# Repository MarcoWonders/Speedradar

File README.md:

# MAR07 SpeedRadar

A battery-powered Doppler speed radar that stands next to (or behind) a long jump runway and shows the athlete's approach speed on a TFT display. The goal is to see whether the run-up speed is consistent from jump to jump.

> **Status: work in progress.** The schematic is complete. The PCB (4 layers, 111 × 49 mm, 4 × M3 holes on a 103 × 41 mm pattern) is routed and passes DRC with no unconnected items. The first boards (V1) were ordered at JLCPCB on 17 November 2026; the fabrication files are in `20_Hardware/MAR07_SpeedRadar/production/`. A first enclosure design exists (see below). A first firmware compiles but has not run on hardware. Nothing has been assembled or tested yet.

## How it works

A CDM324 24 GHz Doppler module outputs a low-level IF signal whose frequency is proportional to the target's radial speed:

```
f_d = 2 · v · f0 / c  ≈  161 Hz per m/s   (f0 = 24.125 GHz)
```

A long jump approach peaks at about 8 to 11 m/s, so the signal of interest is roughly 100 Hz to 1.8 kHz. The analog front end amplifies it, a microcontroller samples it, and an FFT picks out the peak frequency.

| Block | Part | Notes |
|---|---|---|
| Radar | CDM324 (24 GHz) | 5 V supply, switched by a P-FET (Q1/Q2) so the MCU can power it down |
| Preamp | LMP7731 | Gain ×130, high-pass ~106 Hz (≈0.66 m/s), low-pass ~6 kHz |
| AGC amp | MAX9814 | Automatic gain control, 50 dB gain setting |
| Anti-alias | RC 4k7 / 10 nF | ~3.4 kHz |
| MCU | Seeed XIAO nRF52840 | ADC on A0, LiPo charger built in, BLE for later |
| 5 V supply | TPS63900 buck-boost | Fed from the switched battery; CFG3 = 36k5 sets 5.0 V |
| Display | 2.79" NV3007 TFT, 142×428, SPI | 8-pin header J4 |
| UI | Power slide switch (SW1), 2 push buttons (SW2/SW3) | Buttons to GND, use the internal pull-ups |

### XIAO pin mapping

| XIAO pin | Function |
|---|---|
| A0 / D0 | Radar signal after the MAX9814 AGC stage (ADC) |
| A1 / D1 | Raw preamp output, before the AGC (ADC, for comparison) |
| D2 / D3 | Display DC / RES |
| D4 / D5 | BTN1 / BTN2 |
| D6 | CDM324 power enable |
| D7 | Display backlight (PWM) |
| D8 / D9 / D10 | Display SCK / CS / MOSI |
| SWD pads (RST/DIO/CLK) | 1.27 mm header J5 |

The display header's pin order (GND, VCC, SCL, SDA, RES, DC, CS, BLK) is taken from vendor listings that don't fully agree. **Check it against the silkscreen on your module before ordering the PCB.** V1 was ordered with this pin order; it still has to be confirmed on the real module.

## Prototype options

The first board revision carries a few extra options so things can be measured and tuned on the bench without a new board:

| Ref | What | Default | Alternative |
|---|---|---|---|
| TP1 to TP9 | Test points: IF, PRE, AGC, ADC, VBAT, +5V, +3.3V, 2× GND loop | - | - |
| JP1 | MAX9814 gain | 1-2 bridged: 50 dB | Open: 60 dB, 2-3: 40 dB |
| FB1, C15 | Filter on the radar's 5 V supply | FB1 = 0R | Fit a ferrite bead if the buck-boost's switching noise shows up in the spectrum |
| R11 / Q3 / R12 | Display backlight drive | R11 0R, GPIO drives BLK directly | Remove R11, fit Q3 (high-side P-FET) and R12; the PWM becomes active-low |
| Q4 | Battery reverse-polarity protection (P-FET, gate to GND) | Fitted | - |
| R13 / C16 | Raw preamp signal to A1 through a 3.4 kHz anti-alias RC | Fitted | - |
| J5 | SWD header (3V3, DIO, CLK, RST, GND) | - | For recovering the bootloader or debugging |

Battery current can be measured with an ammeter across the power switch (SW1) while it's off.

## Firmware

`30_Firmware/SpeedRadar/` is an Arduino sketch for the XIAO nRF52840.

- Board package: **Seeed nRF52 Boards** (the non-mbed one), board "Seeed XIAO nRF52840".
- Library: **GFX Library for Arduino** (Arduino_GFX) 1.6.x, for the NV3007 display.
- Build from the command line: `arduino-cli compile -b Seeeduino:nrf52:xiaonRF52840 30_Firmware/SpeedRadar`

What it does:
- Samples A0 at 8 kHz, takes 1024 samples (128 ms per frame), runs an FFT and picks the strongest peak between 100 and 2400 Hz.
- Shows the speed in large digits, the maximum speed since the last reset, and the battery voltage.
- BTN1 resets the maximum. BTN2 switches between km/h and m/s.
- At boot it feeds a synthetic 10 m/s tone through the analysis and shows `selftest PASS` or `FAIL`.
- Prints one CSV line per frame over USB serial: `Hz, m/s, SNR, valid, late samples`. Use this for tuning on the bench.

The tuning values (sample rate, frequency band, SNR threshold, SPI speed) sit together near the top of `SpeedRadar.ino`.

The display's CS line is on D9, which is also the XIAO's default SPI MISO pin. The firmware therefore gives the SPI peripheral an unused internal pin as MISO and drives D9 as CS.

## Placement

Put the radar **behind the landing pit**, pointing back up the runway and as close to the runway's line as possible. A radar only measures the speed component toward itself. From beside the runway, the angle changes as the athlete passes, so the reading changes even if the athlete's speed doesn't. From behind the pit, the take-off board is about 10 to 12 m away, which is within the CDM324's useful range, and the angle error stays under about 0.5%.

## Repository layout

```
20_Hardware/MAR07_SpeedRadar/   KiCad 9 project (schematic + PCB)
30_Firmware/SpeedRadar/         Arduino sketch for the XIAO nRF52840
30_Mechanical/                  3D-printed enclosure: concept drawing (enclosure_v0.svg)
                                generated by enclosure_drawing.py (parameters in PCB coordinates)
                                shell.stl, lid.stl, button_cap.stl generated by enclosure_3d.py
```

> **Enclosure STLs are unverified.** They pass an automatic collision check, but that check uses estimated dimensions. Measure these on the real parts and update the parameters before printing: display glass position and stack height (assumed 15 mm above the PCB), radar antenna height in its socket (14.6 mm), shield can height (4 mm), tact switch height (5 mm), and the SW1 body and lever position.

The KiCad project uses some third-party libraries: the PCM "AKL" libraries, SamacSys parts (TPS63900, SRN3015 inductor, SMS-210F shield), and a Seeed XIAO nRF52840 symbol. Install them through KiCad's Plugin and Content Manager or from the vendors before opening the project.

## Credits

The analog front end is based on **limpkin's CDM324 Doppler Motion Sensor Backpack**:
[CDM324 Doppler Motion Sensor Backpack, now with FFTs!](https://www.limpkin.fr/index.php?post/2022/03/31/CDM324-Doppler-Motion-Sensor-Backpack,-now-with-FFTs!)
The LMP7731 preamp, the MAX9814 AGC stage and the general approach come from that design. Thanks for publishing it in such detail.

Changes in this project compared with that design:
- Adapted for a long jump runway: a higher input high-pass and a lower anti-alias corner, matched to running speeds.
- A Seeed XIAO nRF52840 as the MCU, with LiPo power and a buck-boost converter for the radar's 5 V.
- A TFT display and buttons for standalone use on the track.

Datasheets (not included in this repository):
- CDM324: search for "CDM324 datasheet" from your module's vendor.
- [TPS63900 (TI)](https://www.ti.com/product/TPS63900)
- [MAX9814 (Analog Devices)](https://www.analog.com/en/products/max9814.html)
- [LMP7731 (TI)](https://www.ti.com/product/LMP7731)
- [XIAO nRF52840 (Seeed)](https://wiki.seeedstudio.com/XIAO_BLE/)

## License

Apache License 2.0, see [LICENSE](LICENSE). You may use, change and build on the hardware, firmware and enclosure files, also commercially, as long as you keep the notices.

The analog front end is based on limpkin's CDM324 backpack, which is MIT licensed; its notice is kept in [NOTICE](NOTICE).

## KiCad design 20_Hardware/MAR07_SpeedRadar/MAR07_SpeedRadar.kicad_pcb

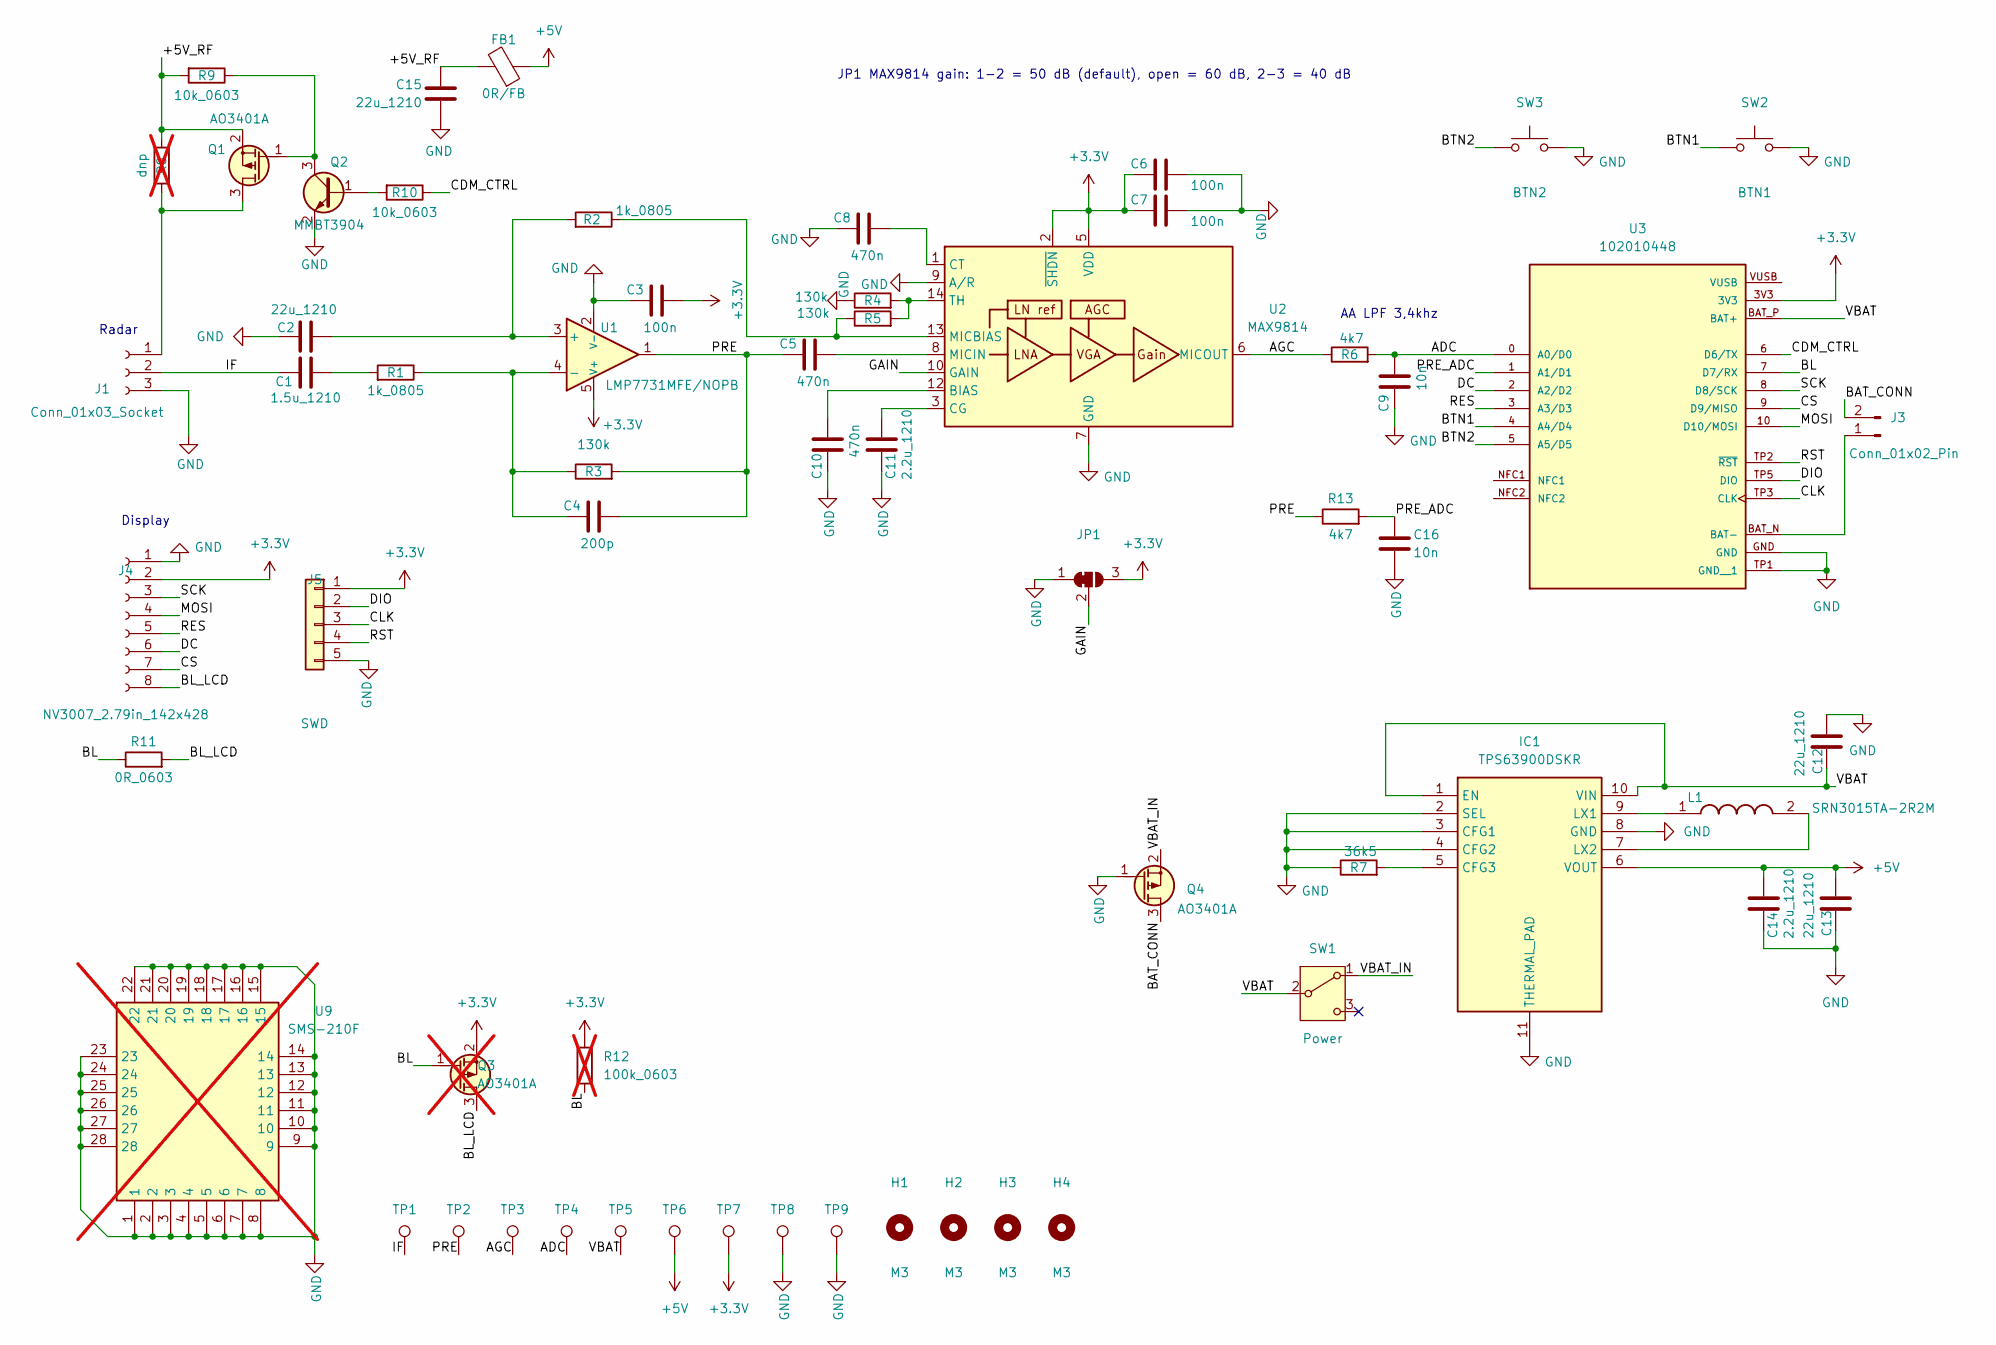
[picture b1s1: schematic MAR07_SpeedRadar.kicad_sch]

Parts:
C1: 1.5u_1210; C_1210_3225Metric; LCSC C342711
C2, C12, C13, C15: 22u_1210; C_1210_3225Metric; LCSC C6120032
C3, C6, C7: 100n; C_0603_1608Metric; LCSC C14663
C4: 200p; C_0603_1608Metric; LCSC C1600
C5, C8, C10: 470n; C_0603_1608Metric; LCSC C1623
C9, C16: 10n; C_0603_1608Metric; LCSC C57112
C11, C14: 2.2u_1210; C_1210_3225Metric; LCSC C1950
FB1: 0R/FB; L_0805_2012Metric; LCSC C17477
H1, H2, H3, H4: M3; MountingHole_3.2mm_M3
IC1: TPS63900DSKR; SON50P250X250X80-11N-D; Mouser Part Number 595-TPS63900DSKR; LCSC C1518762
J1: Conn_01x03_Socket; PinSocket_1x03_P2.54mm_Vertical
J3: Conn_01x02_Pin; JST_PH_S2B-PH-K_1x02_P2.00mm_Horizontal; LCSC C173752
J4: NV3007_2.79in_142x428; PinSocket_1x08_P2.54mm_Vertical
J5: SWD; PinHeader_1x05_P1.27mm_Vertical; LCSC C2689177
JP1: GAIN_SEL; SolderJumper-3_P1.3mm_Bridged12_RoundedPad1.0x1.5mm
L1: SRN3015TA-2R2M; SRN3015TA2R2M; Mouser Part Number 652-SRN3015TA-2R2M; LCSC C5362464
Q1, Q4: AO3401A; SOT-23; LCSC C15127
Q2: MMBT3904; SOT-23; LCSC C20526
Q3: AO3401A; SOT-23; LCSC C15127; not fitted
R1, R2: 1k_0805; R_0805_2012Metric; LCSC C17513
R3, R4, R5: 130k; R_0603_1608Metric_Pad0.98x0.95mm_HandSolder; LCSC C22795
R6, R13: 4k7; R_0603_1608Metric_Pad0.98x0.95mm_HandSolder; LCSC C23162
R7: 36k5; R_0603_1608Metric_Pad0.98x0.95mm_HandSolder; LCSC C23029
R8: dnp; R_0603_1608Metric_Pad0.98x0.95mm_HandSolder; not fitted
R9, R10: 10k_0603; R_0603_1608Metric_Pad0.98x0.95mm_HandSolder; LCSC C25804
R11: 0R_0603; R_0603_1608Metric_Pad0.98x0.95mm_HandSolder; LCSC C21189
R12: 100k_0603; R_0603_1608Metric_Pad0.98x0.95mm_HandSolder; LCSC C25803; not fitted
SW1: Power; SW_Slide_SPDT_Angled_CK_OS102011MA1Q; LCSC C226259
SW2: BTN1; SW_PUSH_6mm; LCSC C2837515
SW3: BTN2; SW_PUSH_6mm; LCSC C2837515
TP1: IF; TestPoint_Pad_D1.5mm
TP2: PRE; TestPoint_Pad_D1.5mm
TP3: AGC; TestPoint_Pad_D1.5mm
TP4: ADC; TestPoint_Pad_D1.5mm
TP5: VBAT; TestPoint_Pad_D1.5mm
TP6: +5V; TestPoint_Pad_D1.5mm
TP7: +3.3V; TestPoint_Pad_D1.5mm
TP8, TP9: GND; TestPoint_Loop_D2.50mm_Drill1.0mm
U1: LMP7731MFE/NOPB; SOT-23-5; LCSC C2870513
U2: MAX9814; DFN-14-1EP_3x3mm_P0.4mm_EP1.78x2.35mm; LCSC C41714
U3: 102010448; MODULE_102010448; PARTREV 2022/08/18; LCSC C17209540
U9: SMS-210F; SMS210F; Mouser Part Number 861-SMS-210F; not fitted

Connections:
+3.3V: C3.1, C6.2, C7.2, J4.2, J5.1, JP1.3 (B), Q3.2 (S), R12.1, TP7.1, U1.5 (V+), U2.2 (~SHDN), U2.5 (VDD), U3.3V3
+5V: C13.2, C14.2, FB1.1, IC1.6 (VOUT), TP6.1
/+5V_RF: C15.1, FB1.2, Q1.2 (S), R8.2, R9.2
/ADC: C9.1, R6.2, TP4.1, U3.0 (A0/D0)
/AGC: R6.1, TP3.1, U2.6 (MICOUT)
/BAT_CONN: J3.2, Q4.3 (D)
/BL: Q3.1 (G), R11.1, R12.2, U3.7 (D7/RX)
/BL_LCD: J4.8, Q3.3 (D), R11.2
/BTN1: SW2.1, U3.4 (A4/D4)
/BTN2: SW3.1, U3.5 (A5/D5)
/CDM_CTRL: R10.1, U3.6 (D6/TX)
/CLK: J5.3, U3.TP3 (CLK)
/CS: J4.7, U3.9 (D9/MISO)
/DC: J4.6, U3.2 (A2/D2)
/DIO: J5.2, U3.TP5 (DIO)
/GAIN: JP1.2 (C), U2.10 (GAIN)
/IF: C1.1, J1.2, TP1.1
/MOSI: J4.4, U3.10 (D10/MOSI)
/PRE: C4.1, C5.2, R3.2, R13.1, TP2.1, U1.1
/PRE_ADC: C16.1, R13.2, U3.1 (A1/D1)
/RES: J4.5, U3.3 (A3/D3)
/RST: J5.4, U3.TP2 (~RST)
/SCK: J4.3, U3.8 (D8/SCK)
/VBAT: C12.1, IC1.1 (EN), IC1.10 (VIN), SW1.2 (B), TP5.1, U3.BAT_P (BAT+)
/VBAT_IN: Q4.2 (S), SW1.1 (A)
GND: C2.1, C3.2, C6.1, C7.1, C8.2, C9.2, C10.2, C11.1, C12.2, C13.1, C14.1, C15.2, C16.2, IC1.2 (SEL), IC1.3 (CFG1), IC1.4 (CFG2), IC1.8 (GND), IC1.11 (THERMAL_PAD), J1.3, J4.1, J5.5, JP1.1 (A), Q2.2 (E), Q4.1 (G), R4.1, R7.1, SW2.2, SW3.2, TP8.1, TP9.1, U1.2 (V-), U2.4 (GND), U2.7 (GND), U2.9 (A/R), U2.11 (GND), U2.15 (GND), U3.GND, U3.TP1 (GND__1), U9.1, U9.2, U9.3, U9.4, U9.5, U9.6, U9.7, U9.8, U9.9, U9.10, U9.11, U9.12, U9.13, U9.14, U9.15, U9.16, U9.17, U9.18, U9.19, U9.20, U9.21, U9.22, U9.23, U9.24, U9.25, U9.26, U9.27, U9.28
unnamed: C1.2, R1.1
unnamed: IC1.5 (CFG3), R7.2
unnamed: IC1.9 (LX1), L1.1
unnamed: IC1.7 (LX2), L1.2
unnamed: J1.1, Q1.3 (D), R8.1
unnamed: J3.1, U3.BAT_N (BAT-)
unnamed: Q1.1 (G), Q2.3 (C), R9.1
unnamed: Q2.1 (B), R10.2
unnamed: C2.2, R2.1, U1.3 (+)
unnamed: C4.2, R1.2, R3.1, U1.4 (-)
unnamed: C10.1, U2.12 (BIAS)
unnamed: C11.2, U2.3 (CG)
unnamed: C8.1, U2.1 (CT)
unnamed: R2.2, R5.1, U2.13 (MICBIAS)
unnamed: C5.1, U2.8 (MICIN)
unnamed: R4.2, R5.2, U2.14 (TH)

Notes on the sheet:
Radar
JP1 MAX9814 gain: 1-2 = 50 dB (default), open = 60 dB, 2-3 = 40 dB
Display
AA LPF 3,4khz

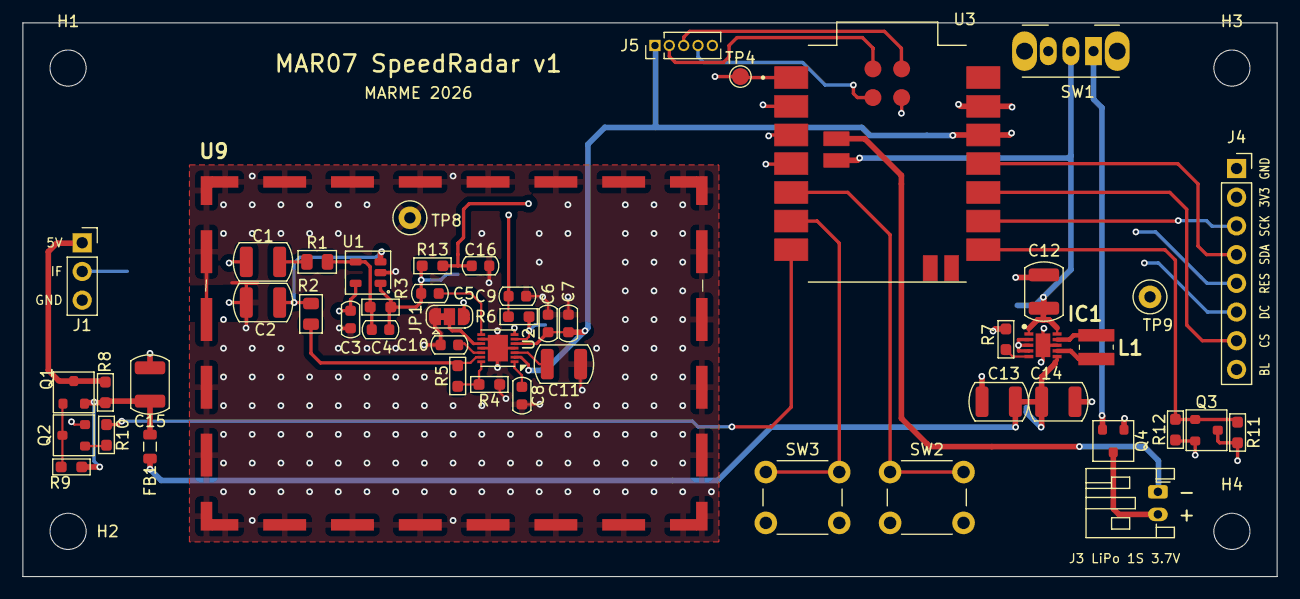
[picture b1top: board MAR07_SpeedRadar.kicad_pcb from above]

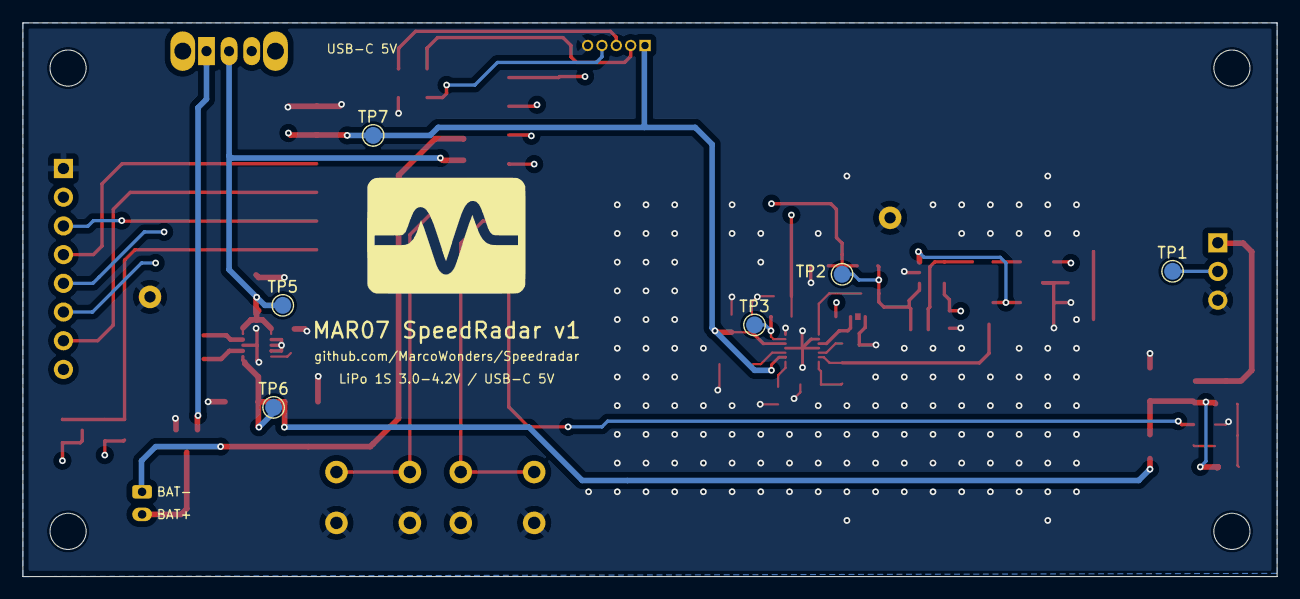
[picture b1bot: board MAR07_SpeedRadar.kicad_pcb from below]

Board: 4 copper layers, 111.0 x 49.0 mm, 62 parts (7 on the bottom side), 42 nets.

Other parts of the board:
LOGO1: LOGO; marmelogo22mm

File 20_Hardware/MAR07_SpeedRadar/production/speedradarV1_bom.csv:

Designator,Footprint,Quantity,Value,LCSC Part #
C1,1210,1,1.5u_1210,C342711
"C10, C5, C8",0603,3,470n,C1623
"C11, C14",1210,2,2.2u_1210,C1950
"C12, C13, C15, C2",1210,4,22u_1210,C6120032
"C16, C9",0603,2,10n,C57112
"C3, C6, C7",0603,3,100n,C14663
C4,0603,1,200p,C1600
FB1,0805,1,0R/FB,C17477
IC1,SON50P250X250X80-11N-D,1,TPS63900DSKR,C1518762
J1,PinSocket_1x03_P2.54mm_Vertical,1,Conn_01x03_Socket,
J3,JST_PH_S2B-PH-K_1x02_P2.00mm_Horizontal,1,Conn_01x02_Pin,C173752
J4,PinSocket_1x08_P2.54mm_Vertical,1,NV3007_2.79in_142x428,
J5,PinHeader_1x05_P1.27mm_Vertical,1,SWD,C2689177
JP1,SolderJumper-3_P1.3mm_Bridged12_RoundedPad1.0x1.5mm,1,GAIN_SEL,
L1,SRN3015TA2R2M,1,SRN3015TA-2R2M,C5362464
"Q1, Q4",SOT-23,2,AO3401A,C15127
Q2,SOT-23,1,MMBT3904,C20526
"R1, R2",0805,2,1k_0805,C17513
"R10, R9",0603,2,10k_0603,C25804
R11,0603,1,0R_0603,C21189
"R13, R6",0603,2,4k7,C23162
"R3, R4, R5",0603,3,130k,C22795
R7,0603,1,36k5,C23029
SW1,SW_Slide_SPDT_Angled_CK_OS102011MA1Q,1,Power,C226259
SW2,SW_PUSH_6mm,1,BTN1,C2837515
SW3,SW_PUSH_6mm,1,BTN2,C2837515
TP1,TestPoint_Pad_D1.5mm,1,IF,
TP2,TestPoint_Pad_D1.5mm,1,PRE,
TP3,TestPoint_Pad_D1.5mm,1,AGC,
TP4,TestPoint_Pad_D1.5mm,1,ADC,
TP5,TestPoint_Pad_D1.5mm,1,VBAT,
TP6,TestPoint_Pad_D1.5mm,1,+5V,
TP7,TestPoint_Pad_D1.5mm,1,+3.3V,
"TP8, TP9",TestPoint_Loop_D2.50mm_Drill1.0mm,2,GND,
U1,SOT-23-5,1,LMP7731MFE/NOPB,C2870513
U2,DFN-14-1EP_3x3mm_P0.4mm_EP1.78x2.35mm,1,MAX9814,C41714
U3,MODULE_102010448,1,102010448,C17209540

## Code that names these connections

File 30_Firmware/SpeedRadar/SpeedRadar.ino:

// MAR07 SpeedRadar firmware: CDM324 Doppler radar -> FFT -> speed on a 2.79" NV3007 TFT.
// Board: Seeed XIAO nRF52840 ("Seeed nRF52 Boards" core 1.1.x, the non-mbed one).
// Library: "GFX Library for Arduino" (Arduino_GFX) 1.6.x.
#include <Arduino_GFX_Library.h>
#include "doppler.h"

// ---- pins (schematic net names in comments)
constexpr int PIN_RADAR_IN = A0;  // /ADC, after the MAX9814 AGC. A1 = /PRE_ADC, raw preamp
constexpr int PIN_TFT_DC = D2;    // /DC
constexpr int PIN_TFT_RST = D3;   // /RES
constexpr int PIN_BTN1 = D4;      // SW2, to GND
constexpr int PIN_BTN2 = D5;      // SW3, to GND
constexpr int PIN_RADAR_EN = D6;  // /CDM_CTRL, HIGH = radar powered (Q2 pulls Q1's gate low)
constexpr int PIN_BL = D7;        // /BL, backlight
constexpr int PIN_TFT_CS = D9;    // /CS (this is the XIAO's MISO pin, see tftSPI below)
constexpr bool BL_ACTIVE_LOW = false;  // true if Q3/R12 are fitted instead of R11

// ---- tuning knobs: adjust on the bench
constexpr int N = 1024;            // FFT size
constexpr float FS = 8000;         // sample rate, Hz -> 128 ms per frame, 7.8 Hz (0.05 m/s) per bin
constexpr float F_MIN = 100;       // Hz, below the front end's ~106 Hz high-pass (0.6 m/s)
constexpr float F_MAX = 2400;      // Hz, ~15 m/s, well above a long jump run-up
constexpr float SNR_MIN = 8;       // peak / band mean needed to count as a target
constexpr int SPI_HZ = 16000000;   // drop to 8 MHz if the display shows garbage

// D9 is wired to the display's CS, but on the XIAO it is also the default SPI MISO.
// The display is write-only, so give the SPI peripheral an unused pin for MISO
// (D18 = P0.11, only used by the IMU on the Sense variant, as an input) and drive D9 as CS.
SPIClass tftSPI(NRF_SPIM3, 18 /* dummy MISO */, D8 /* SCK */, D10 /* MOSI */);
Arduino_DataBus *bus = new Arduino_HWSPI(PIN_TFT_DC, PIN_TFT_CS, &tftSPI);
Arduino_GFX *gfx = new Arduino_NV3007(bus, PIN_TFT_RST, 1 /* landscape */, false, 142, 428,
                                      12, 0, 14, 0, nv3007_279_init_operations,
                                      sizeof(nv3007_279_init_operations));

uint16_t samples[N];
float re[N], im[N];
float vmax = 0;  // peak speed since the last reset, m/s
bool kmh = true;
volatile bool btn1 = false, btn2 = false;

// 200 ms lockout against contact bounce
void onBtn1() { static uint32_t t; if (millis() - t > 200) { t = millis(); btn1 = true; } }
void onBtn2() { static uint32_t t; if (millis() - t > 200) { t = millis(); btn2 = true; } }

// Paced capture: one analogRead every 1/FS. Returns how many samples were late.
int capture() {
  const uint32_t period = 1000000UL / FS;
  int late = 0;
  uint32_t t = micros();
  for (int i = 0; i < N; i++) {
    if ((int32_t)(micros() - t) > (int32_t)period) late++;
    while ((int32_t)(micros() - t) < 0) {}
    t += period;
    samples[i] = analogRead(PIN_RADAR_IN);
  }
  return late;
}

float batteryVolts() {
  // XIAO divider 1M / 510k on P0.31, enabled by VBAT_ENABLE low (set once in setup)
  return analogRead(PIN_VBAT) * 3.6f / 4096 * 1510.0f / 510.0f;
}

// Feed a synthetic 10 m/s tone through the real analysis path.
bool selfTest() {
  const float hz = 10 * doppler::HZ_PER_MPS;
  for (int i = 0; i < N; i++)
    samples[i] = 2048 + 300 * sinf(2 * (float)M_PI * hz * i / FS) + random(-40, 40);
  doppler::Peak p = doppler::analyse(samples, re, im, N, FS, F_MIN, F_MAX, SNR_MIN);
  const bool ok = p.valid && fabsf(p.hz - hz) < FS / N / 2;
  Serial.printf("selftest: want %.1f Hz, got %.1f Hz snr %.1f -> %s\n", hz, p.hz, p.snr, ok ? "PASS" : "FAIL");
  return ok;
}

void drawSpeed(float mps, bool valid) {
  char s[8];
  const float f = kmh ? 3.6f : 1.0f;
  gfx->setTextColor(valid ? RGB565_WHITE : RGB565_DARKGREY, RGB565_BLACK);
  gfx->setTextSize(10);  // 60x80 px per character
  gfx->setCursor(4, 10);
  snprintf(s, sizeof s, "%5.1f", mps * f);
  gfx->print(s);

  gfx->setTextColor(RGB565_YELLOW, RGB565_BLACK);
  gfx->setTextSize(3);
  gfx->setCursor(4, 108);
  snprintf(s, sizeof s, "%5.1f", vmax * f);
  gfx->print("max ");
  gfx->print(s);
  gfx->setTextColor(RGB565_LIGHTGREY, RGB565_BLACK);
  gfx->setCursor(320, 108);
  gfx->print(kmh ? "km/h" : "m/s ");
}

void drawBattery(float v) {
  char s[8];
  snprintf(s, sizeof s, "%.2fV", v);
  gfx->setTextSize(2);
  gfx->setTextColor(v < 3.5f ? RGB565_RED : RGB565_DARKGREY, RGB565_BLACK);
  gfx->setCursor(360, 4);
  gfx->print(s);
}

void setup() {
  pinMode(PIN_RADAR_EN, OUTPUT);
  digitalWrite(PIN_RADAR_EN, HIGH);
  pinMode(PIN_BL, OUTPUT);
  digitalWrite(PIN_BL, BL_ACTIVE_LOW ? LOW : HIGH);
  pinMode(VBAT_ENABLE, OUTPUT);
  digitalWrite(VBAT_ENABLE, LOW);  // keep LOW: when HIGH, P0.31 can see the full battery voltage
  pinMode(PIN_CHARGING_CURRENT, OUTPUT);
  digitalWrite(PIN_CHARGING_CURRENT, LOW);  // 100 mA charging instead of 50 mA
  pinMode(PIN_BTN1, INPUT_PULLUP);
  pinMode(PIN_BTN2, INPUT_PULLUP);
  attachInterrupt(digitalPinToInterrupt(PIN_BTN1), onBtn1, FALLING);
  attachInterrupt(digitalPinToInterrupt(PIN_BTN2), onBtn2, FALLING);

  analogReference(AR_DEFAULT);  // 0..3.6 V
  analogReadResolution(12);

  Serial.begin(115200);
  gfx->begin(SPI_HZ);
  gfx->fillScreen(RGB565_BLACK);
  gfx->setTextSize(3);
  gfx->setCursor(4, 10);
  gfx->setTextColor(RGB565_WHITE);
  gfx->println("MAR07 SpeedRadar");
  const bool ok = selfTest();
  gfx->setTextColor(ok ? RGB565_GREEN : RGB565_RED);
  gfx->println(ok ? "selftest PASS" : "selftest FAIL");
  delay(1500);
  gfx->fillScreen(RGB565_BLACK);
  drawBattery(batteryVolts());
}

void loop() {
  static uint32_t lastBat = 0;
  const int late = capture();
  const doppler::Peak p = doppler::analyse(samples, re, im, N, FS, F_MIN, F_MAX, SNR_MIN);
  const float mps = p.valid ? p.hz / doppler::HZ_PER_MPS : 0;
  if (mps > vmax) vmax = mps;

  if (btn1) { btn1 = false; vmax = 0; }   // BTN1: reset max
  if (btn2) { btn2 = false; kmh = !kmh; } // BTN2: km/h <-> m/s

  drawSpeed(mps, p.valid);
  if (millis() - lastBat > 5000) {
    lastBat = millis();
    drawBattery(batteryVolts());
  }
  // CSV for bench tuning: Hz, m/s, SNR, valid, late samples
  Serial.printf("%.1f,%.2f,%.1f,%d,%d\n", p.hz, mps, p.snr, p.valid, late);
}
